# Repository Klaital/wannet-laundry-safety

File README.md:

# wannet-laundry-safety
Arduino device for monitoring for water leaks and temperature in the laundry machines.

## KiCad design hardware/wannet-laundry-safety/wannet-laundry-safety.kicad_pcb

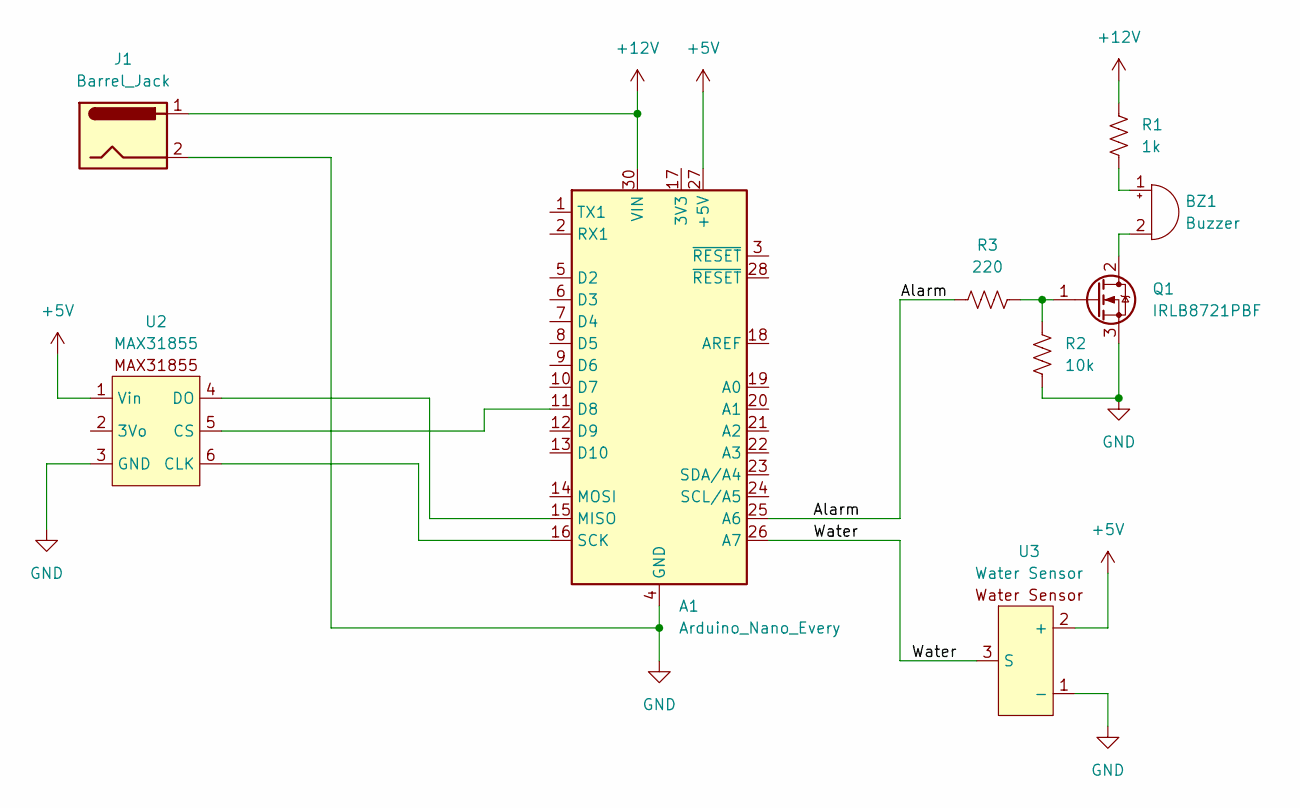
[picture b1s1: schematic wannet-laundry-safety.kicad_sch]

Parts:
A1: Arduino_Nano_Every; Arduino_Nano
BZ1: Buzzer; JST_PH_B2B-PH-K_1x02_P2.00mm_Vertical
J1: Barrel_Jack; TerminalBlock_bornier-2_P5.08mm
Q1: IRLB8721PBF; TO-220-3_Vertical
R1: 1k; R_0805_2012Metric_Pad1.20x1.40mm_HandSolder
R2: 10k; R_0805_2012Metric_Pad1.20x1.40mm_HandSolder
R3: 220; R_0805_2012Metric_Pad1.20x1.40mm_HandSolder
U2: MAX31855; MAX31855_thermocouple_breakout
U3: Water Sensor; JST_PH_B3B-PH-K_1x03_P2.00mm_Vertical

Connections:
+5V: A1.27 (+5V), U2.1 (Vin), U3.2 (+)
+12V: A1.30 (VIN), J1.1, R1.1
/Alarm: A1.25 (A6), R3.1
/Water: A1.26 (A7), U3.3 (S)
GND: A1.4 (GND), A1.29 (GND), J1.2, Q1.3 (S), R2.2, U2.3 (GND), U3.1 (-)
unnamed: A1.11 (D8), U2.5 (CS)
unnamed: A1.15 (MISO), U2.4 (DO)
unnamed: A1.16 (SCK), U2.6 (CLK)
unnamed: BZ1.1 (+), R1.2
unnamed: BZ1.2 (-), Q1.2 (D)
unnamed: Q1.1 (G), R2.1, R3.2

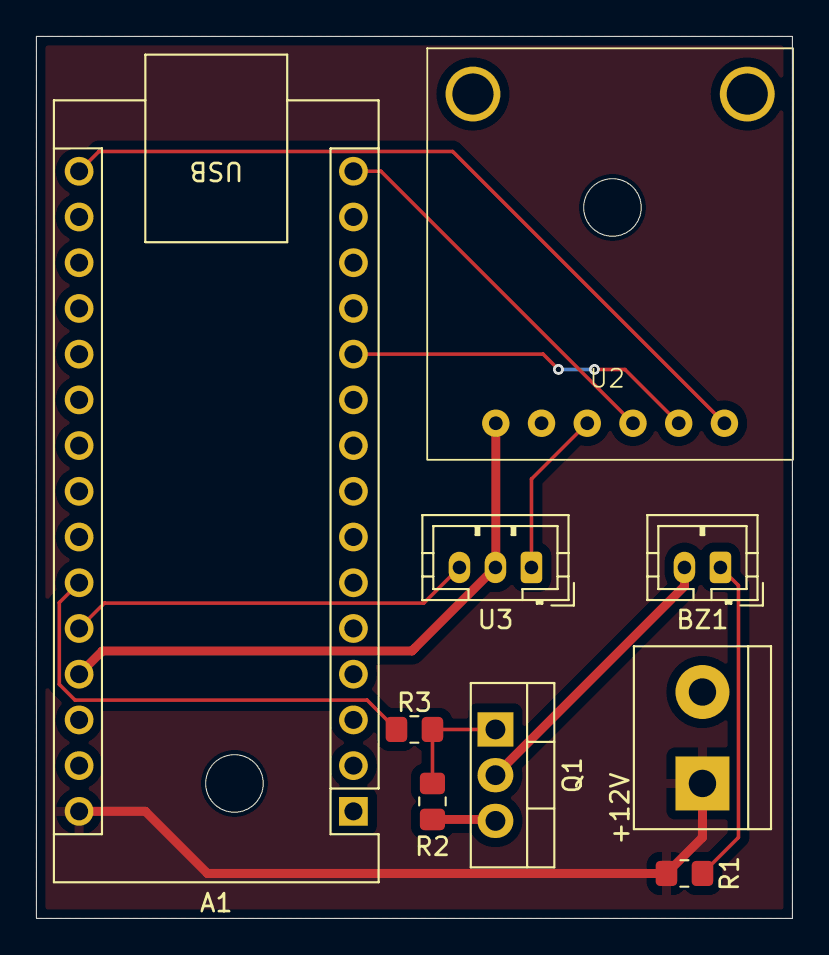
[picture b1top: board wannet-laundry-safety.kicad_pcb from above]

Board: 2 copper layers, 42.0 x 49.0 mm, 9 parts (0 on the bottom side), 11 nets.

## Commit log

2025-01-29 Enabling sensors and alarm
2025-02-07 Adding hardware design
